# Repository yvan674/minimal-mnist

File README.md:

# Minimal MNIST

A very small fully connected neural network able to classify images from the MNIST database.
The purpose is to better understand how to use the `hpoptim` package and experimenting with creating an architecture using bayesian optimization techniques.

The network is optimized using Bayesian Optimization and HyperBand (BOHB) to find the best hyperparameters.

## Goals

The goal is to create a very small network that can classify images from MNIST.
The number of output dimensions and activations for the first two layers, as well as the optimizer type, learning rate, and momentum are chosen using BOHB.

## Best configuration

The following configuration yields a validation accuracy of 94.5% after just 10 epochs.

| Item                      | Parameter         | Value              |
|---------------------------|-------------------|--------------------|
| 1st Fully Connected Layer | Input             | Flattened 28 x 28  |
|                           | Output dimensions | 11                 |
|                           | Activation        | ReLU               |
| 2nd Fully Connected Layer | Output dimensions | 11                 |
|                           | Activation        | ReLU               |
| Optimizer                 | Type              | SGD                |
|                           | Learning Rate     | 0.0038795787201773 |
|                           | Momentum          | 0.9409782496856666 |

## Physical Model

Owing to the simplicity of the model, I have chosen to create a physical version of this neural network.
The hardware for this can be found in the [physical-nn](github.com/yvan674/physical-nn) repo.

For the physical neural network representation, I chose to use a 10-15-10 layer architecture (i.e. output dim of 10, 15, 10 on the first, second and final layers respectively) as it looked more aesthetically appealing.

### Numpy and Torch

As the plan for running the model physically will use a Raspberry Pi Zero W, a numpy version of the model has also been included.

## Visualization

Model prediction visualization can be done using `visualizer.py`.
This script visualizes the input from MNIST, the network prediction, and the network activations in the model.

## Dependencies

- numpy>=1.18
- pillow~=7.1
- pytorch>=1.5

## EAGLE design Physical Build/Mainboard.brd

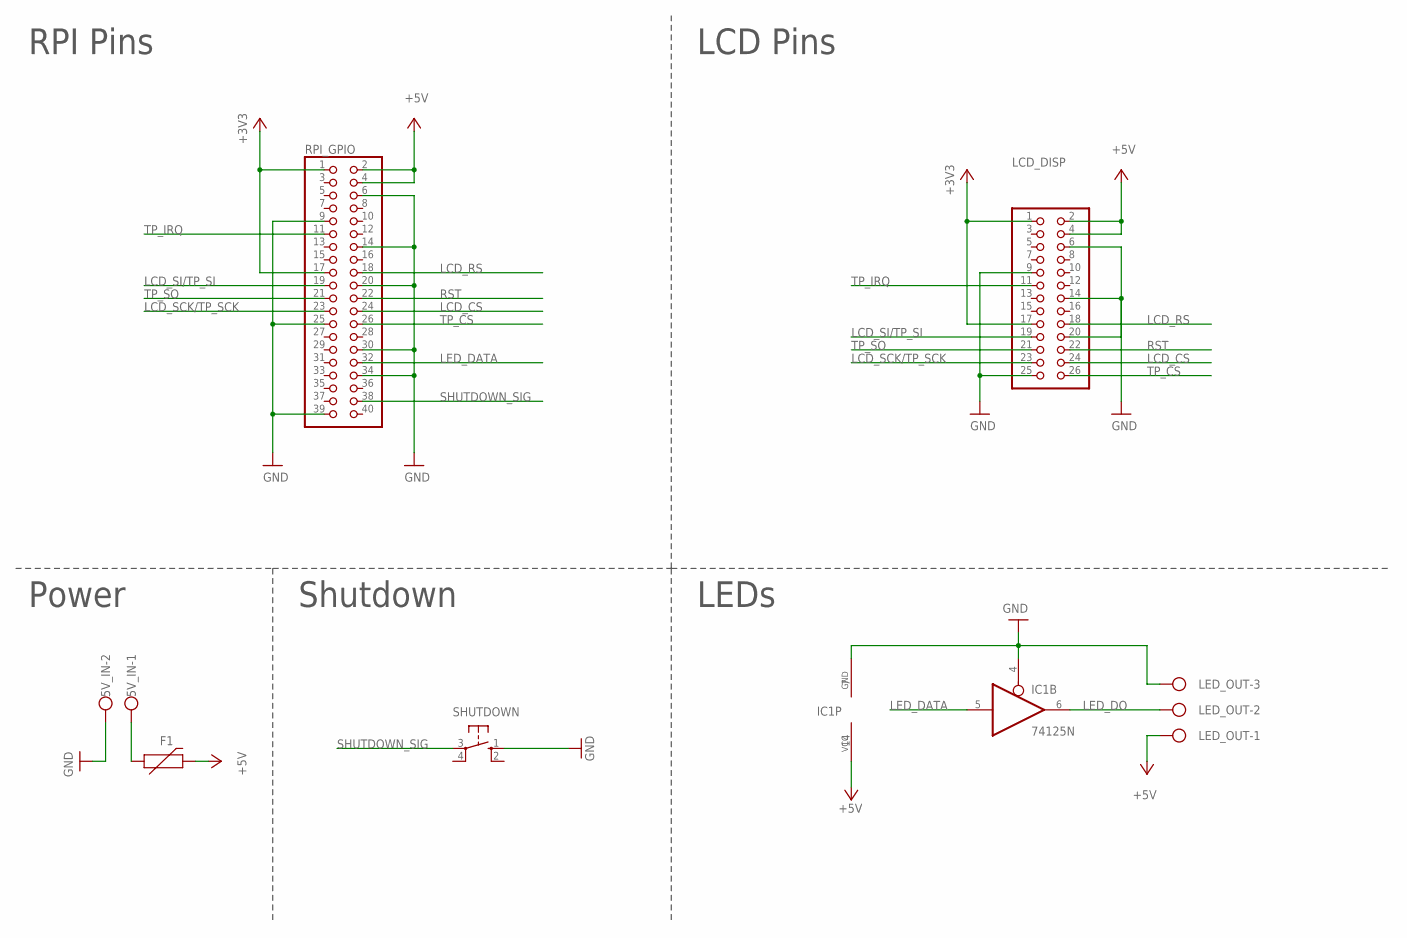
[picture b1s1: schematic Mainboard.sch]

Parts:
5V_IN: W237-102
F1: JK30-500
IC1: 74125N; DIL14
LCD_DISP: PINHD-2X13; 2X13
LED_OUT: W237-103
RPI_GPIO: PINHD-2X20; 2X20
SHUTDOWN: 40-XX; B3F-40XX

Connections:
+3V3: LCD_DISP.1, LCD_DISP.17, RPI_GPIO.1, RPI_GPIO.17
+5V: F1.P$2 (2), IC1.14 (VCC), LCD_DISP.2, LCD_DISP.4, LED_OUT.1, RPI_GPIO.2, RPI_GPIO.4
GND: 5V_IN.2, IC1.4 (OE), IC1.7 (GND), LCD_DISP.6, LCD_DISP.9, LCD_DISP.14, LCD_DISP.20, LCD_DISP.25, LED_OUT.3, RPI_GPIO.6, RPI_GPIO.9, RPI_GPIO.14, RPI_GPIO.20, RPI_GPIO.25, RPI_GPIO.30, RPI_GPIO.34, RPI_GPIO.39, SHUTDOWN.1 (S)
LCD_CS: LCD_DISP.24, RPI_GPIO.24
LCD_RS: LCD_DISP.18, RPI_GPIO.18
LCD_SCK/TP_SCK: LCD_DISP.23, RPI_GPIO.23
LCD_SI/TP_SI: LCD_DISP.19, RPI_GPIO.19
LED_DATA: IC1.5 (I), RPI_GPIO.32
LED_DO: IC1.6 (O), LED_OUT.2
unnamed: 5V_IN.1, F1.P$1 (1)
RST: LCD_DISP.22, RPI_GPIO.22
SHUTDOWN_SIG: RPI_GPIO.38, SHUTDOWN.3
TP_CS: LCD_DISP.26, RPI_GPIO.26
TP_IRQ: LCD_DISP.11, RPI_GPIO.11
TP_SO: LCD_DISP.21, RPI_GPIO.21

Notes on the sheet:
Power
Shutdown
RPI Pins
LCD Pins
LEDs

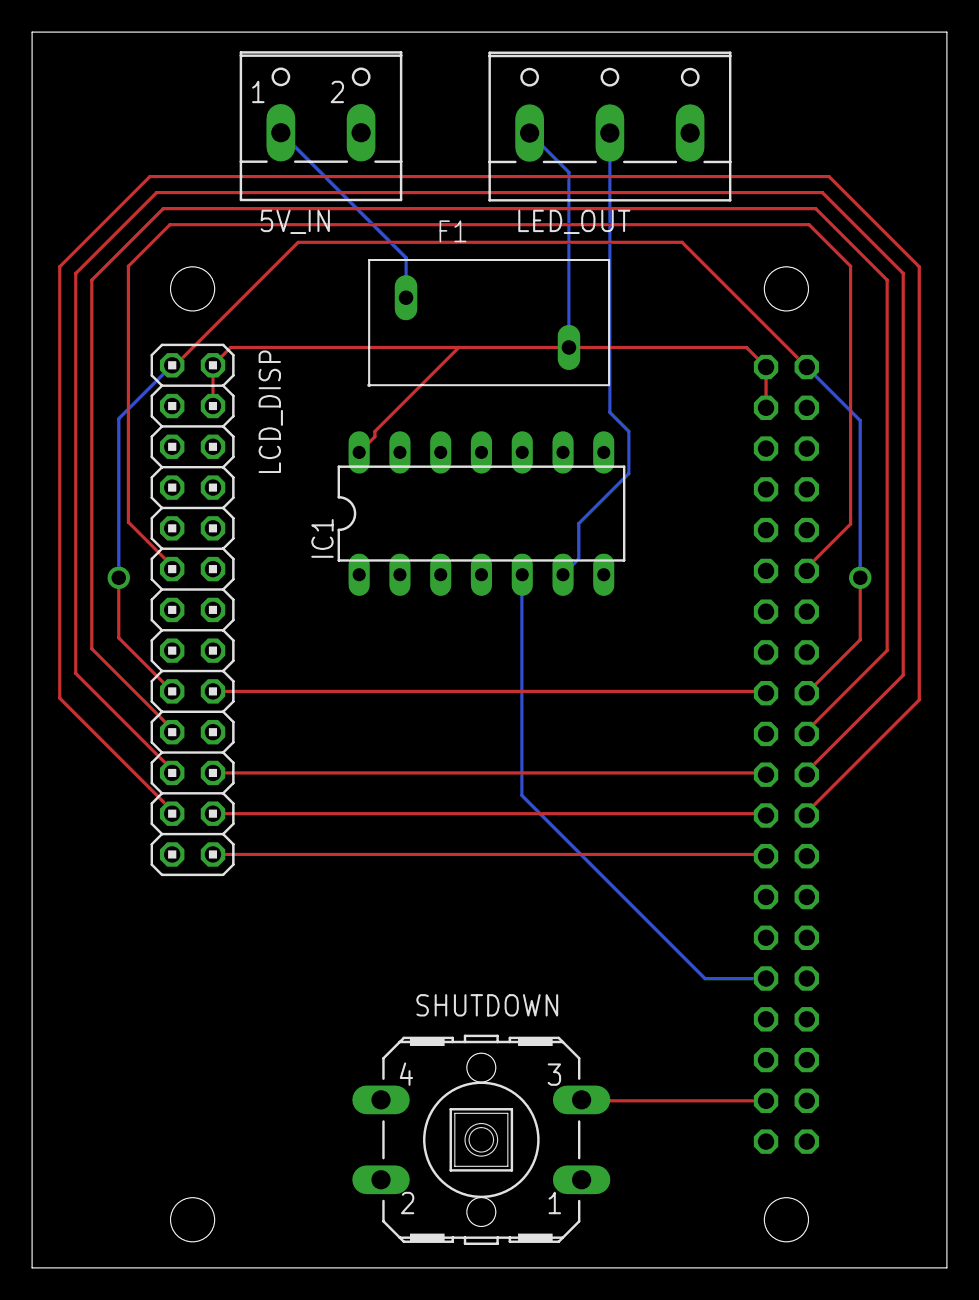
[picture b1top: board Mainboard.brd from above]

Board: 2 copper layers, 57.0 x 77.0 mm, 7 parts (1 on the bottom side), 15 nets.

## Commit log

2019-10-21 Hyperparameter optimization implemented
2019-10-23 Changed the way the Leaky ReLU was encoded
2019-10-23 Made imports relative
2019-10-23 Hyperparameter optimization works
2019-10-29 Hyperparameter exploration
2019-10-29 Trainer can train and save weights
2019-10-30 Minimal inference has been added
2020-04-03 added inference and made some stuff work on older versions of python
2020-04-03 Working visualizer GUI
2020-04-03 Added best-model state_dict
2020-04-07 Made it possible to train using weights and biases
2020-04-07 PEP8 Compliance
2020-04-07 small fixes
2020-04-07 Rename to not interfere with wandb package
2020-04-07 Added layer minimization criterion
2020-04-07 Added grad clip
2020-04-10 Completely functional with and without torch
2020-04-10 Minor tweaks
2020-04-12 added connections between neurons
2020-04-14 Minor fixes to visualizer.py
2020-05-18 Fixed minor issues with imports and numpy only compatibility
2020-05-19 Initial implementation of physical.py
2020-05-19 Minor cleanup to visualizer.py
2020-08-19 Working physical.py
2020-08-19 Initial work on drawer.py
2020-08-20 Added files for the physical build
2020-08-23 Added best-model.npy and removed physical build files
2021-01-09 Minor change to dataset error message
2021-01-09 Made inference more robust by removing absolute paths
2021-05-12 Added startup_sequence.py
2021-05-12 Removed Physical Build files and updated README.md to reflect changes
2021-05-12 Updated physical.py to include the startup sequence
2021-05-23 Minor changes
2021-05-23 Use a sine function for animation instead of a counter
2021-05-23 Bug fixes for newly updated animation calculation and added image display
2021-05-27 Graceful startup and shutdown implemented

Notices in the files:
parts and their libraries:
SparkFun-Aesthetics: Licensing: Creative Commons ShareAlike 4.0 International - https://creativecommons.org/licenses/by-sa/4.0
